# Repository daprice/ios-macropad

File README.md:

# Airpad
A tiny (3x4 key) bluetooth keypad using low profile mechanical keyboard switches and the Adafruit Feather 32u4 Bluefruit, intended to give you quick access to functions on your iOS device that are normally cumbersome to use. Or a companion to a 60% or smaller keyboard. Your choice.

[  ](http://www.keyboard-layout-editor.com/#/gists/3676b2810c4b6d54954320ad40bb4f09)

## PCB
Find the [KiCad](http://kicad-pcb.org) source files in the PCB folder.

### Switches
This PCB uses mechanical keyswitches compatible with Kailh PG1350, commonly known as "Choc" Low Profile. These are available in various varieties and in small quantities from vendors like [NovelKeys](https://novelkeys.xyz) in the US.

### Gerber and drill files
The files in `PCB/gerbers` were produced by KiCad 4.0.7 using [OSH Park's recommended settings](https://docs.oshpark.com/design-tools/kicad/generating-kicad-gerbers/). If you have the PCB manufactured somewhere else, you may change the names of the files at the very least (your board house should provide their desired filenames and any special settings they require).

## Acrylic case
The case is currently a work in progress; further documentation will be provided when it's complete.

## Firmware
Firmware will be based on [QMK](http://qmk.fm).

------------------------

This work is licensed under a [Creative Commons Attribution-ShareAlike 4.0 International License](http://creativecommons.org/licenses/by-sa/4.0/).

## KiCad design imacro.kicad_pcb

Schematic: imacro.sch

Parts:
D0:0, D0:1, D0:2, D1:0, D1:1, D1:2, D2:0, D2:1, D2:2, D3:0, D3:1, D3:2: 1N4148; D_SOD-123
D1: MBR120; D_SOD-123F
QI1: QI_Receiver; QI_connector
SW0:0, SW0:1, SW0:2, SW1:0, SW1:1, SW1:2, SW2:0, SW2:1, SW2:2, SW3:0, SW3:1, SW3:2: Choc; PG1350
SW1: TOGGLE; GPTS_SPST_Pushbutton
U1: Feather32u4Bluefruit

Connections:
/5V_USB: D1.1, U1.3
/COL0: D0:0.1, D1:0.1, D2:0.1, D3:0.1, U1.9
/COL1: D0:1.1, D1:1.1, D2:1.1, D3:1.1, U1.15
/COL2: D0:2.1, D1:2.1, D2:2.1, D3:2.1, U1.14
/ROW0: SW0:0.1, SW0:1.1, SW0:2.1, U1.5
/ROW1: SW1:0.1, SW1:1.1, SW1:2.1, U1.6
/ROW2: SW2:0.1, SW2:1.1, SW2:2.1, U1.7
/ROW3: SW3:0.1, SW3:1.1, SW3:2.1, U1.19
GND: QI1.2, SW1.1 (A), U1.25
unnamed: D0:0.2, SW0:0.2
unnamed: D0:1.2, SW0:1.2
unnamed: D0:2.2, SW0:2.2
unnamed: D1.2, QI1.1
unnamed: D1:0.2, SW1:0.2
unnamed: D1:1.2, SW1:1.2
unnamed: D1:2.2, SW1:2.2
unnamed: D2:0.2, SW2:0.2
unnamed: D2:1.2, SW2:1.2
unnamed: D2:2.2, SW2:2.2
unnamed: D3:0.2, SW3:0.2
unnamed: D3:1.2, SW3:1.2
unnamed: D3:2.2, SW3:2.2
unnamed: SW1.2 (B), U1.2

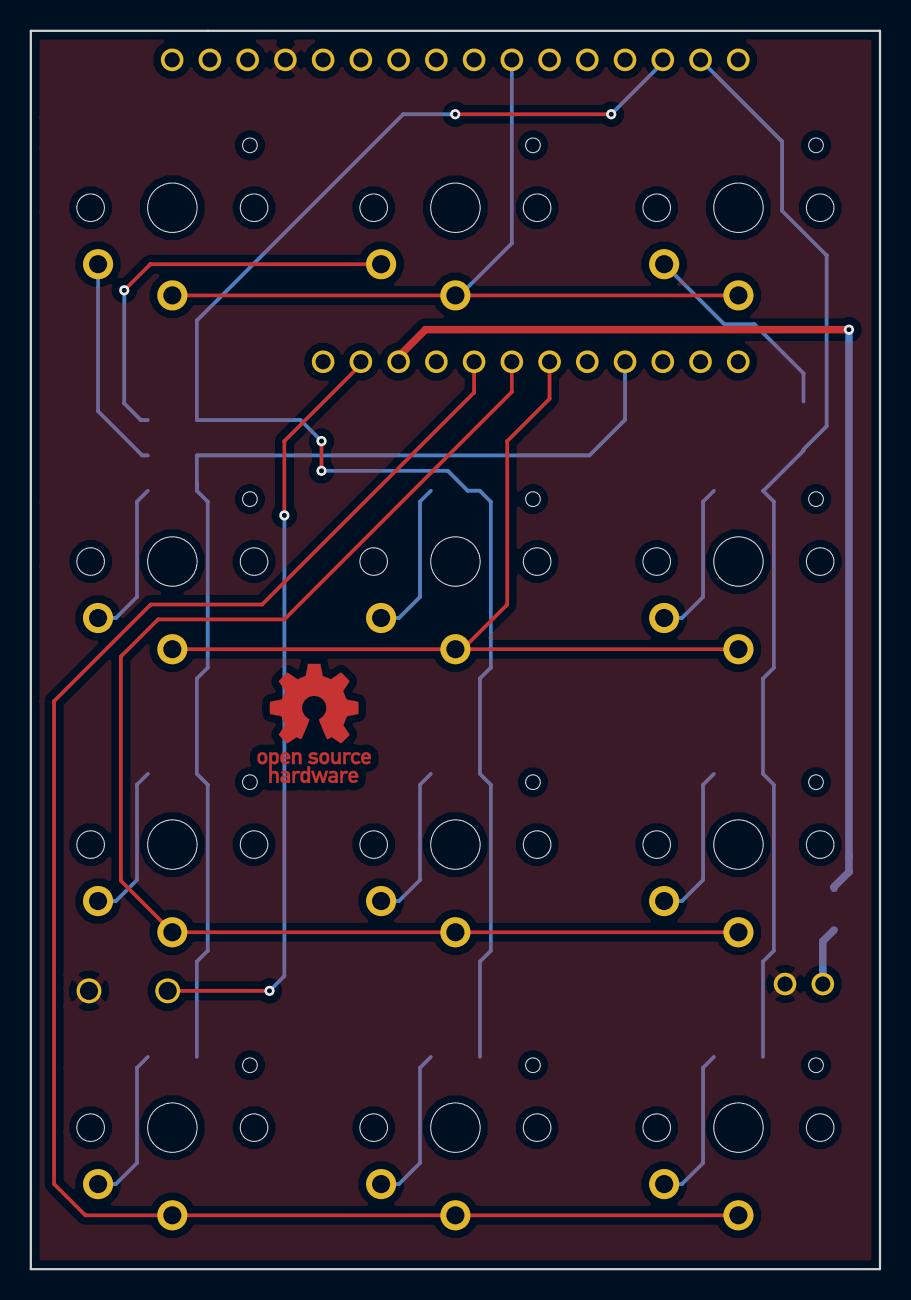
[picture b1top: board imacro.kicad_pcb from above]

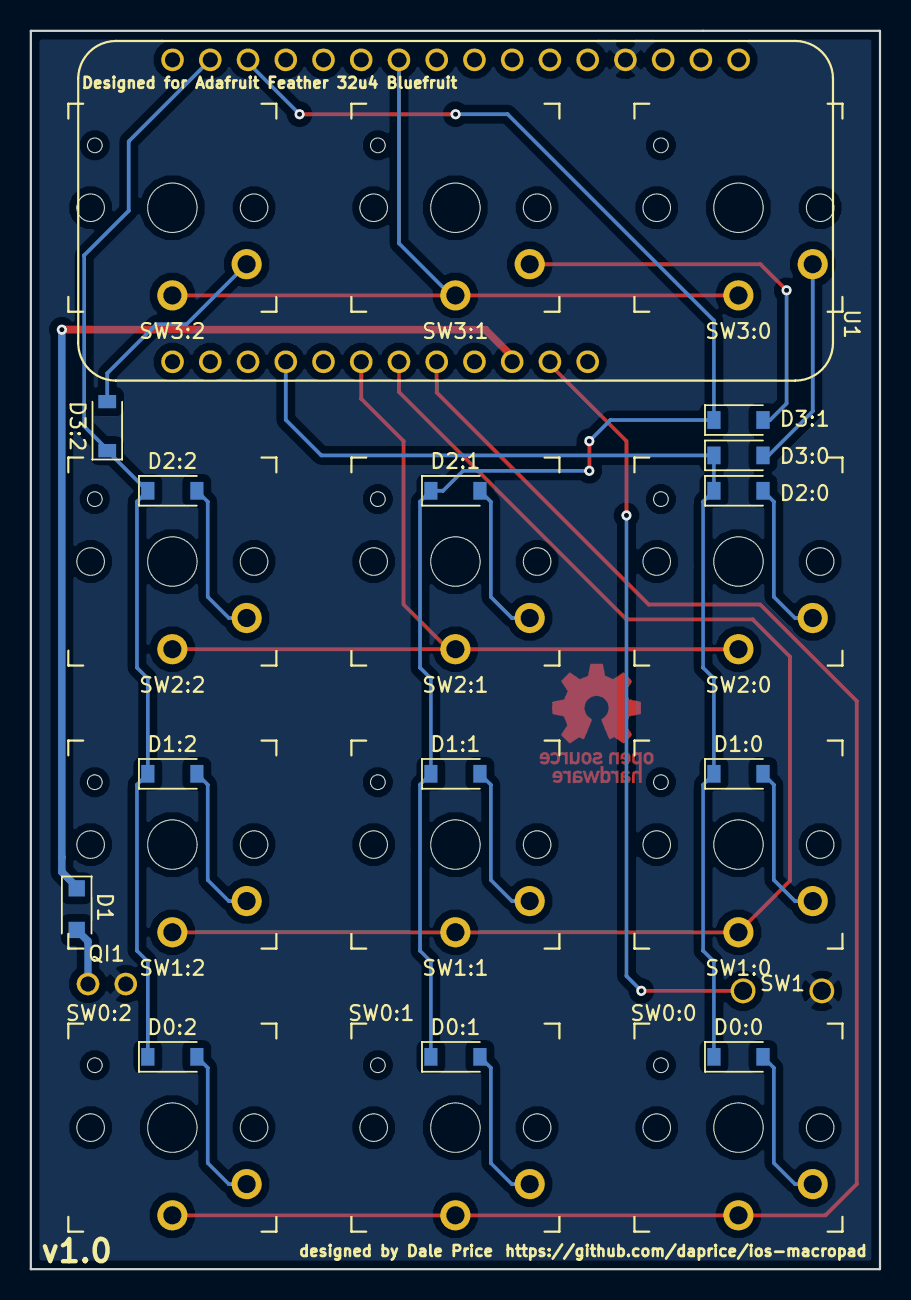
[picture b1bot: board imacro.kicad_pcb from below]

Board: 2 copper layers, 57.2 x 83.3 mm, 28 parts (16 on the bottom side), 23 nets.

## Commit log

2018-02-22 initial commit of schematic and footprint for the feather32u4
2018-02-22 add footprint for kailh pg1350 switch
2018-02-23 create board layout
2018-02-23 Finish PCB layout; add necessary footprints to library; adjust pad drill size for key switches
2018-02-23 adjust some text on the silkscreen
2018-02-23 adjust mask clearance to OSH Park spec
2018-02-24 update gitignore to ignore more backup files
2018-02-24 Don’t use pin 9 on the feather so it can be used to read the battery level
2018-02-25 accomodate smaller case; rotate Feather board around for new battery cable position; improve trace routing somewhat
2018-02-26 Move D0:0 for power button clearance
2018-02-26 Add BoM
2018-02-28 organize project folders; generate gerber files; add readme
2018-03-07 Create OpenSCAD templates for case design
2018-03-07 Create basic layer shape and bolt holes
2018-03-07 position and size screw holes correctly
2018-03-12 Change name to “Airpad”
2018-03-17 Design upper 2 layers of acrylic case using keyboard_parts library; add 3d-rendered layout of layers to assembly.scad for 3d printing prototypes; define key layout
2018-03-17 Add layout preview
2018-03-21 Improve switch footprints (requires daprice/keyswitches.pretty ); increase annular ring size on other footprints; add positive indicator to Qi charger connection
2018-04-08 initial design for layers 0-3
2018-04-08 make rudimentary 3d printable case model
2018-04-08 Widen side bezels for rigidity;
    When using laser cut layers, the thinner side bezels would squeeze in easily when holding the keypad. Now they shouldn’t.
2019-11-07 Open PCB in Kicad v5 and let it do its thing to update stuff (I think it did?)
2019-11-10 Update keyboard_parts library
2019-11-10 Update keyboard_parts lib; define and pass key unit size as required by this library version
2019-11-12 Adjust case layout and size to accommodate 18x17 key spacing (better for kailh choc caps)
2019-11-12 Render the new case size/spacing to STL
2020-01-13 Update to newer keyswitch footprint library version; update SPST pushbutton footprint to include component outline in silkscreen
2020-01-15 Redo PCB layout with condensed (18x17mm) key spacing; adjust power button location on case to match new PCB; suffix version number on PCB with “-c” to indicate condensed variant
2020-01-15 Restore accidentally deleted “Designed for Adafruit Feather…” text; adjust spacing of some silkscreen elements
2020-01-17 Clean up some tracks and make sure vias aren’t below components
2020-01-17 Clean up some traces; avoid vias in power trace; avoid vias under components
2020-01-17 Update version number
2020-01-20 Stitch ground fills to reduce ground loops
2020-01-22 Add stitching vias in ground fill
2020-01-22 Generate updated gerber and drill files
2020-01-22 Generate updated gerber and drill files for condensed version
2020-03-26 Slightly increase clearance around keycaps to accommodate the slightly off center caps I got from MKUltra
2020-03-26 Add flexible button presser cover
2020-03-26 Render STLs

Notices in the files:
README.md:
CC BY-SA 4.0
